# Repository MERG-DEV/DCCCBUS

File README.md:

# dcccbus
MERG CBUS for model railway control - PIC18 Assembler CBUS for DCCCBUS module.

Requires inclusion as a Git submodule of cbuslib_asm (as cbuslib).
Builds as an MPLABX project.

# Copyright and Licensing
[MERG Copyright Notice](https://www.merg.org.uk/resources/copyright)

Shield: [![CC BY-NC-SA 4.0][cc-by-nc-sa-shield]][cc-by-nc-sa]

This work is licensed under a
[Creative Commons Attribution-NonCommercial-ShareAlike 4.0 International License][cc-by-nc-sa].

[![CC BY-NC-SA 4.0][cc-by-nc-sa-image]][cc-by-nc-sa]

[cc-by-nc-sa]: http://creativecommons.org/licenses/by-nc-sa/4.0/
[cc-by-nc-sa-image]: https://licensebuttons.net/l/by-nc-sa/4.0/88x31.png
[cc-by-nc-sa-shield]: https://img.shields.io/badge/License-CC%20BY--NC--SA%204.0-lightgrey.svg

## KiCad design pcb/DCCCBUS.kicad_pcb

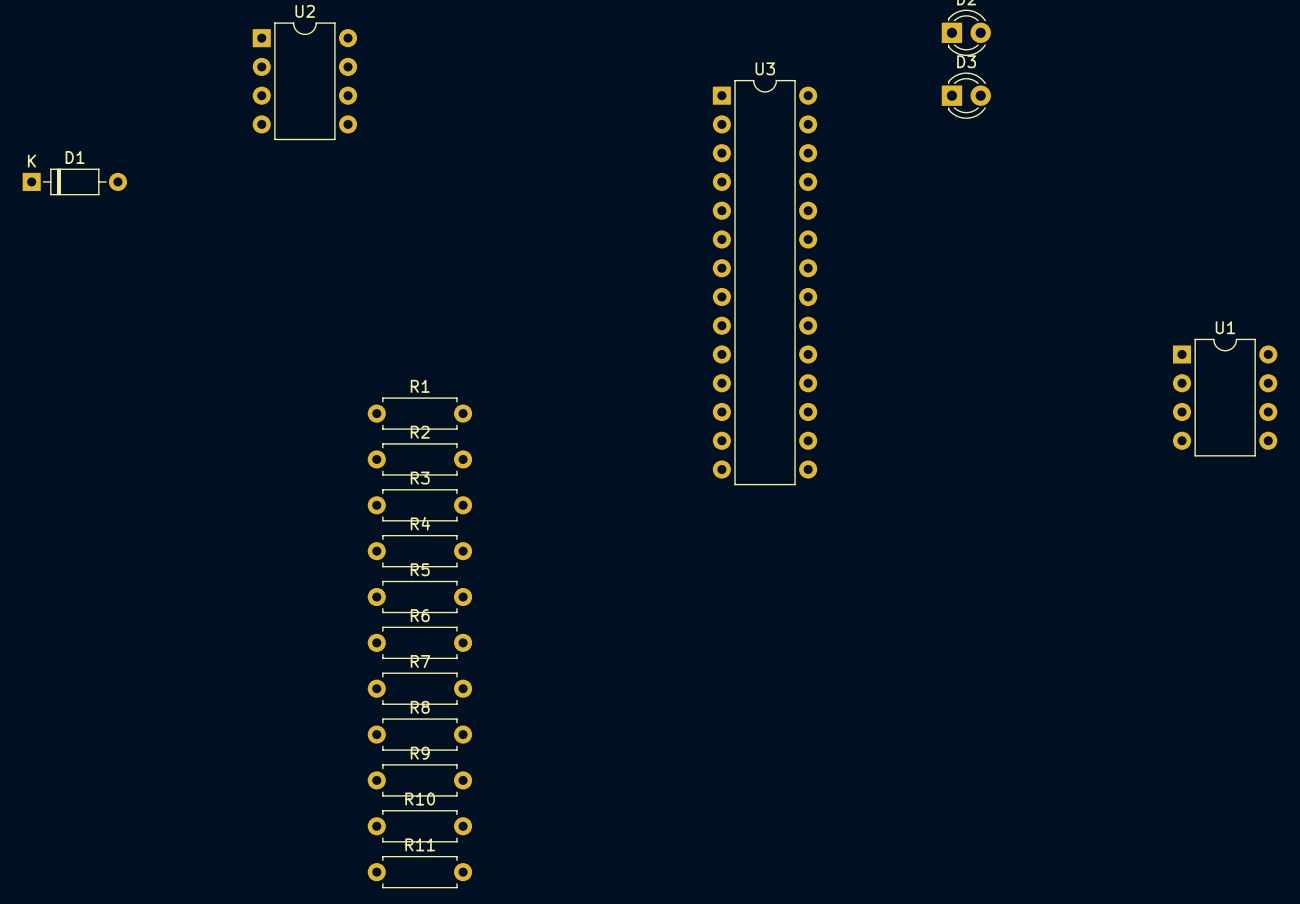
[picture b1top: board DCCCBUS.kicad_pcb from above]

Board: 2 copper layers, 17 parts (0 on the bottom side), 17 nets, no tracks yet.

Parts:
D1: 1N4148; D_DO-35_SOD27_P7.62mm_Horizontal
D2: Yellow; LED_D3.0mm
D3: Green; LED_D3.0mm
R1, R2, R3, R4, R10, R11: 10K; R_Axial_DIN0207_L6.3mm_D2.5mm_P7.62mm_Horizontal
R5: 1K5; R_Axial_DIN0207_L6.3mm_D2.5mm_P7.62mm_Horizontal
R6: 100K; R_Axial_DIN0207_L6.3mm_D2.5mm_P7.62mm_Horizontal
R7: 100R; R_Axial_DIN0207_L6.3mm_D2.5mm_P7.62mm_Horizontal
R8, R9: 1K8; R_Axial_DIN0207_L6.3mm_D2.5mm_P7.62mm_Horizontal
U1: MCP2551-I-P; DIP-8_W7.62mm
U2: 6N137; DIP-8_W7.62mm
U3: PIC18F2480-ISP; DIP-28_W7.62mm

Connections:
+5V: R1.1, R2.1, R3.1, R4.1, R10.1, R11.1, U1.3 (VDD), U2.7 (EN), U2.8 (VCC), U3.20 (VDD)
GND: R6.2, R7.2, R8.2, R9.2, U1.2 (VSS), U2.5 (GND), U3.8 (VSS)
unnamed: D1.1 (K), U2.2 (A)
unnamed: D2.2 (A), U3.27 (RB6/KBI2/PGC)
unnamed: D2.1 (K), R8.1
unnamed: D3.2 (A), U3.28 (RB7/KBI3/PGD)
unnamed: D3.1 (K), R9.1
unnamed: R3.2, U3.18 (RX/DT/RC7)
unnamed: R2.2, U3.17 (TX/CK/RC6)
unnamed: R11.2, U3.16 (SDO/RC5)
unnamed: U1.4 (RXD), U3.23 (RB2/INT2/CANTX)
unnamed: R6.1, U1.8 (Rs)
unnamed: U1.1 (TXD), U3.24 (RB3/CANRX)
unnamed: R5.1, U2.3 (C)
unnamed: R1.2, U2.6 (VO), U3.21 (RB0/AN10/INT0)
unnamed: R10.2, U3.7 (RA5/AN4/~SS/HLVDIN)
unnamed: R4.2, U3.1 (Vpp/~MCLR/RE3)

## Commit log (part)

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2025-06-05 Created new MPLABX project with empty source file.
2025-06-05 Added cbuslib, latest refactor, sub module.
2025-06-25 Failing SLiM initialisation test.
2025-08-03 Passing SLiM boot test.
2025-08-03 Removed unecessary includes.
2025-08-03 Failing SLiM receive RTR test.
2025-08-09 Use M4 frozen state file instead of lots of includes, changed M4 included files suffix from inc to m4i and removed dependency files for inclusion of these in macro files.
2025-08-09 Corrected test name.
2025-08-09 Boot test passing with CAN configuration.
2025-08-10 Datmode not used.
2025-08-10 Not yet ready for RTR tests.
2025-08-10 Extract test name from M4 filename.
2025-08-10 Macro to set test name from M4 filename.
2025-08-10 Added boot into bootloader test.
2025-08-10 Tidied code, use banksel instead of direct wrtie, use port output latch registers for bit twiddling.
2025-08-10 Clear all data memeory banks on initialisation.
2025-09-17 Little bit of tidying up.
2025-09-17 Generate input of DCC preamble, but nothing else yet.
2025-09-18 Input a basic accessory packet, without checksum, for a CBUS event number.
2025-09-18 Input a basic accessory packet with checksum
2025-09-18 Refactored basic accessory packet input.
2025-09-20 Replaced hard coded vectors in bootloader for user initialisation and interrupts with simple symbol declerations.
2025-09-23 Receive 3 byte DCC packet.
2025-09-23 Verify checksum and fixed bits of first and second bytes.
2025-09-23 Macros for explicit actication or deactivation of individual output (output maps to event number), or actvation of one of pair of outputs (output pair maps to event number, output of pair maps to ASO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
2025-09-23 Ensure executable is up to date before running tests.
2025-09-23 Corrected 0 half bit timing values.
2025-09-24 Silenced make.
2025-09-24 Report tests that fail to launch.
2025-09-24 Corrected encoding of accessory packet.
2025-09-24 Decoding accessory packet to CBUS opcode and event number.
2025-09-25 Annotated packet decoding to event number.
2025-09-27 Always set activation bit when using toggling pairs.
2025-09-27 Clean M4 freeze state files.
2025-09-27 Use log macro instead of raw report statements.
2025-09-27 Combine confirmation of not other mode into wait for mode.
2025-09-27 Transmit CBUS message for DCC packet.
2025-09-28 Moved DCC macros into separate file. Moved some macros to more appropriate files.
2025-09-28 Renamed intial DCC packet test.
2025-09-28 Compile fails if variable RAM allocation beyond end of Bank 0.
2025-09-28 Macros to isolate high and low bytes of 16 bit values.
2025-09-28 Split long line.
2025-09-28 Corrected spelling in comment.
2025-09-28 Ignore DCC basic accessory packets longer than two bytes, ignoring checksum.
2025-09-28 Ignore DCC basic accessory packets with bad checksum.
2025-09-28 Ignore DCC basic accessory packets with preamble too short.
2025-09-28 Refactored basic accessory packet generation.
2025-09-28 Corrected refactored basic accessory packet generation.
2025-09-28 Ignore DCC basic accessory packets with invalid first byte.
2025-09-28 Ignore DCC basic accessory packets with invalid second byte.
2025-09-28 Ignore DCC basic accessory packets shorter than two bytes, ignoring checksum.
2025-09-29 Changed name to distinguish testing basic accessory packets for toggle pair output.
2025-09-29 For basic paired outputs activation bit in second byte should always be set.
2025-09-29 Shuffled code and added or changed labels to make intention clearer.
2025-09-29 Verify checksum in DCC bit interrupt. Ignore packets not having exactly three bytes.
2025-09-29 Replace On and Off with Activate and Deactivate to reflect terms used in DCC specifications.
2025-09-29 Added individually addressed, rather than pair orientated, DCC packets to verify mapping to CBUS.
2025-09-29 Refactor main loop into subroutines to proccess a new DCC packet, a bad DCC packet, and a new DCC byte.
2025-09-29 Renamed constants and variables plus modified comments to make intention clearer.
2025-09-30 Implemented queue for 16 DCC packets.
2025-10-01 Implemented queue for Tx of 16 CBUS event messages as well as Rx of 16 DCC packets.
2025-10-01 Prevent overwriting queued packet not yet verified.
2025-10-01 Initialisation is to start seeking preamble for first DCC packet on next rising edge.
2025-10-01 Packet end bit counts as preamble.
2025-10-02 Moved byte storage into interrupt handler.
2025-10-02 Queues given complete, separate, banks.
2025-10-02 Advancing queue indices simplified by wrapping from 255 to 0.
2025-10-03 Moved into interrupt copying received DCC bytes to packet and enqueing received DCC packet.
2025-10-03 Substitute in tstfsz.
2025-10-03 Substitute in decfsz.
2025-10-03 Reworked insert and extract offset handling along with detection of when slots full or emptied. Moved some handling into interrupt to simplify main loop.
2025-10-03 Tweaked test.
2025-10-03 Derive transmitted frame size from CBUS opcode.
2025-10-04 No need to check if packet Rx queue slot is useable before storing byte as this is done at start of byte.
2025-10-04 Move received byte directly from shift register into packt Rx queue slot.
2025-10-04 Skip DCC packet if too many bytes received to fit into Rx queue slot.
2025-10-06 Packets longer than queue slot skipped, so length of packet can be derived from insert offset, so no need for received byte counter.
2025-10-06 Renamed RAM clear subroutine.
2025-10-06 Use insert and extract offsets to detect when queues are full or empty rather than testing first byte of slot to see if slot contains useable data.
2025-10-07 Received DCC packet length now stored in laste byte of queue slot. Received bits now shifted direcltly into slot bytes instead of via Rx shift register.
2025-10-07 Corrected test for empty Rx queue at start of enqueue event for Tx.
2025-10-07 DCC packet Rx queue now 64 slots each of 4 bytes. CBUS event Tx queue now 32 slots each of 8 bytes.
2025-10-08 Renamed test as some apply to both basic and extended DCC accessory packets and some apply to either paired or individual output addressing.
2025-10-08 Actually use DCC activation bit instead of expecting to always be set. Activating first output = deactivating second output and vice versa.
2025-10-08 Can generate CBUS events for either complimentary output pairs or individually addressed outputs.
2025-10-08 Reject DCC extended accessory packets with malformed second byte.
2025-10-08 Process extended accessory packet to CBUS ASON1.
2025-10-08 Verify extended packets with invalid checksum are ignored.
2025-10-08 Verify extended packets that overrun slot are ignored.
2025-10-08 Verify extended packets that are too short are ignored.
2025-10-09 Revert to reset and interrupt vector redirection values to avoid user code in boot block.
2025-10-09 Changed CBUS event Tx queue to be 64 slots of 4 bytes each.
2025-10-10 Raise Tx message priority on repeated lost arbitration errors.
2025-11-04 Removed offset between DCC accessory address and CBUS event number, i.e. event 0 no longer mapped to accessory 4 (DCC address 1).
2025-11-05 Moved paired outputs mode input to RC7. Added RCN-213 Linear Addressing input to RC6, not yet implemented address mapping for this.
2025-11-05 Implemented RCN-213 Linear Address mapping.
2025-11-06 Renamed project from DCCCAN to DCCCBUS.
2025-11-10 For now ignore doc directory containing hardware design.
2025-11-10 Paired outputs and RCN-213 linear address selection inputs now active low.
2025-11-12 RCN-213 linear addressing can be used with extended accessory packets.
2025-11-12 In pair addressing mode DCC packets with activation bit, C, not set are ignored.
2025-11-12 Renames basic packet RCN-213 linear addressing test.
2025-11-12 Ignore immediately repeated DCC packets.
2025-11-14 Corrected SID to match CANCAB, i.e. 1.
2025-11-14 Deal with all Tx error interrupts. Keep Rx FIFO flushed, discarding all received CAN frames.
2025-11-15 Pulled down latest defintions from MERG github and added DCCCBUS as a module type on own branch.
2025-11-15 CAN Tx error moved to low priority interrupt.
2025-11-16 Pulled cbusdefs version 8y from MERG-DEV. Removed MTYP_DCCCBUS, using MTYP_CANDEV.
2025-11-16 Added license to repository.
2025-11-17 Renamed submodule cbuslib to cbuslib_asm to align with upstream repository name.
2025-11-17 Used defined names for port pin numbers instead of literals. Added explanatory comments to conversion of DCC accessory output address to CBUS event number.
2025-11-22 Added mode to apply same address offset as CANCMD, 4, selected by setting RC5 low.
2025-11-24 Changed mode selection input pins.
2025-11-24 Test Tx arbitration increases priority with Tx messages in queue.
2025-11-24 Renamed test for raised priority on Tx arbitration failure.
2025-11-24 Refactored Tx wait if not ready test. Replaced nested ifelse calulation of Tx frame length with recursive macro.
2025-11-27 Test, and check, of data not Tx specific.
2025-11-27 Check for Tx ready moved into Tx error interrupt test macros, both before and after interrupt.
2025-11-27 Used special arguments and shift macro to tidy up passing on arguments.
2025-11-27 Factored out common Tx interrupt test macro code.
2025-11-27 Receive CAN frames uusing Rx FIFO.
2025-11-27 Added Rx queue for up to 16 CBUS messages, all discarded for now.
2025-12-08 Added electronics design files.
2025-12-10 Deleted unused MDB macros copied from other projects.
2025-12-10 Added M4 base file as prerequisite of freeze file.
2025-12-10 Renamed files to make explicit when dealing with CAN Rx or Tx.
2025-12-10 Prepended can_ to macors making it explicit when dealing with CAN Rx or Tx.
2025-12-10 Harmonised order of DCC packet values. Ensured key rollovers as well as start and end of range tested.
2025-12-12 Use new cbuslib_asm macros for CAN Rx and Tx.
2025-12-17 Moved custom KiCad symbols into own library. Assigned footprint to resistors in schematic.
2026-01-25 Use relative path to make submodules navigable on github.
